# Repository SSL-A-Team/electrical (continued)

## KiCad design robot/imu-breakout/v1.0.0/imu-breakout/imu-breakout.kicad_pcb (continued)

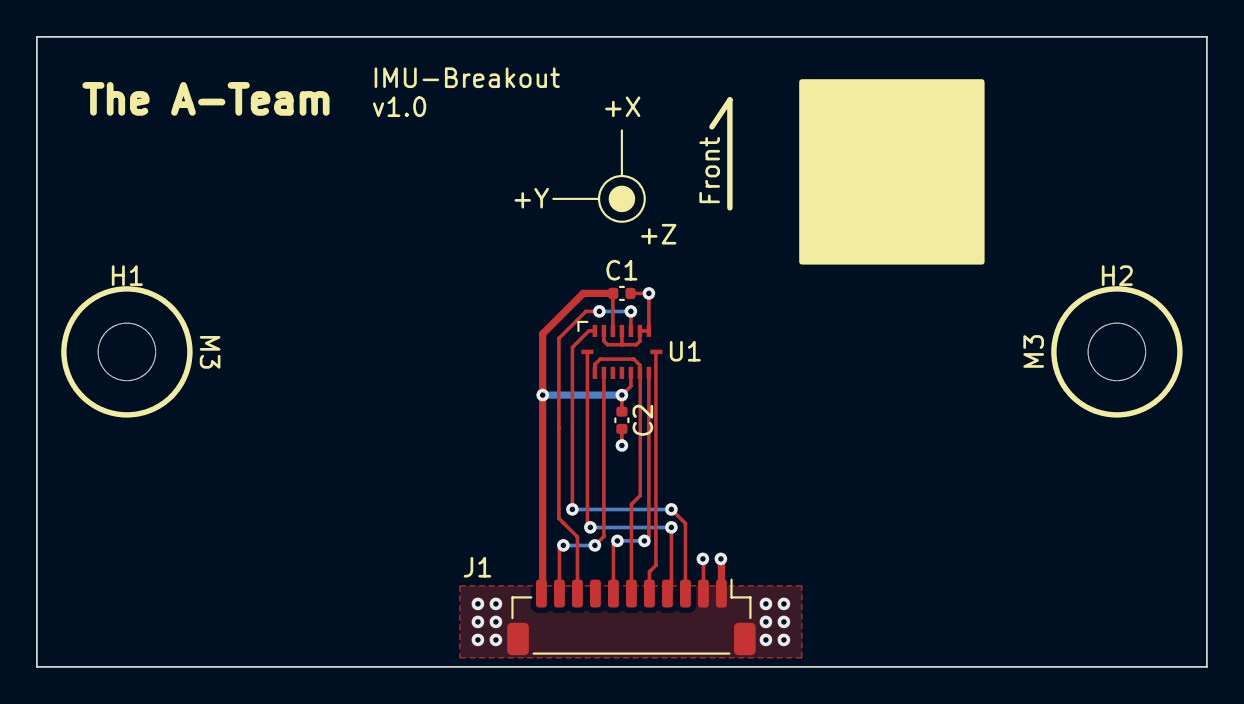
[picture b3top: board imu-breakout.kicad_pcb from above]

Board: 2 copper layers, 65.0 x 35.0 mm, 6 parts (0 on the bottom side), 9 nets.

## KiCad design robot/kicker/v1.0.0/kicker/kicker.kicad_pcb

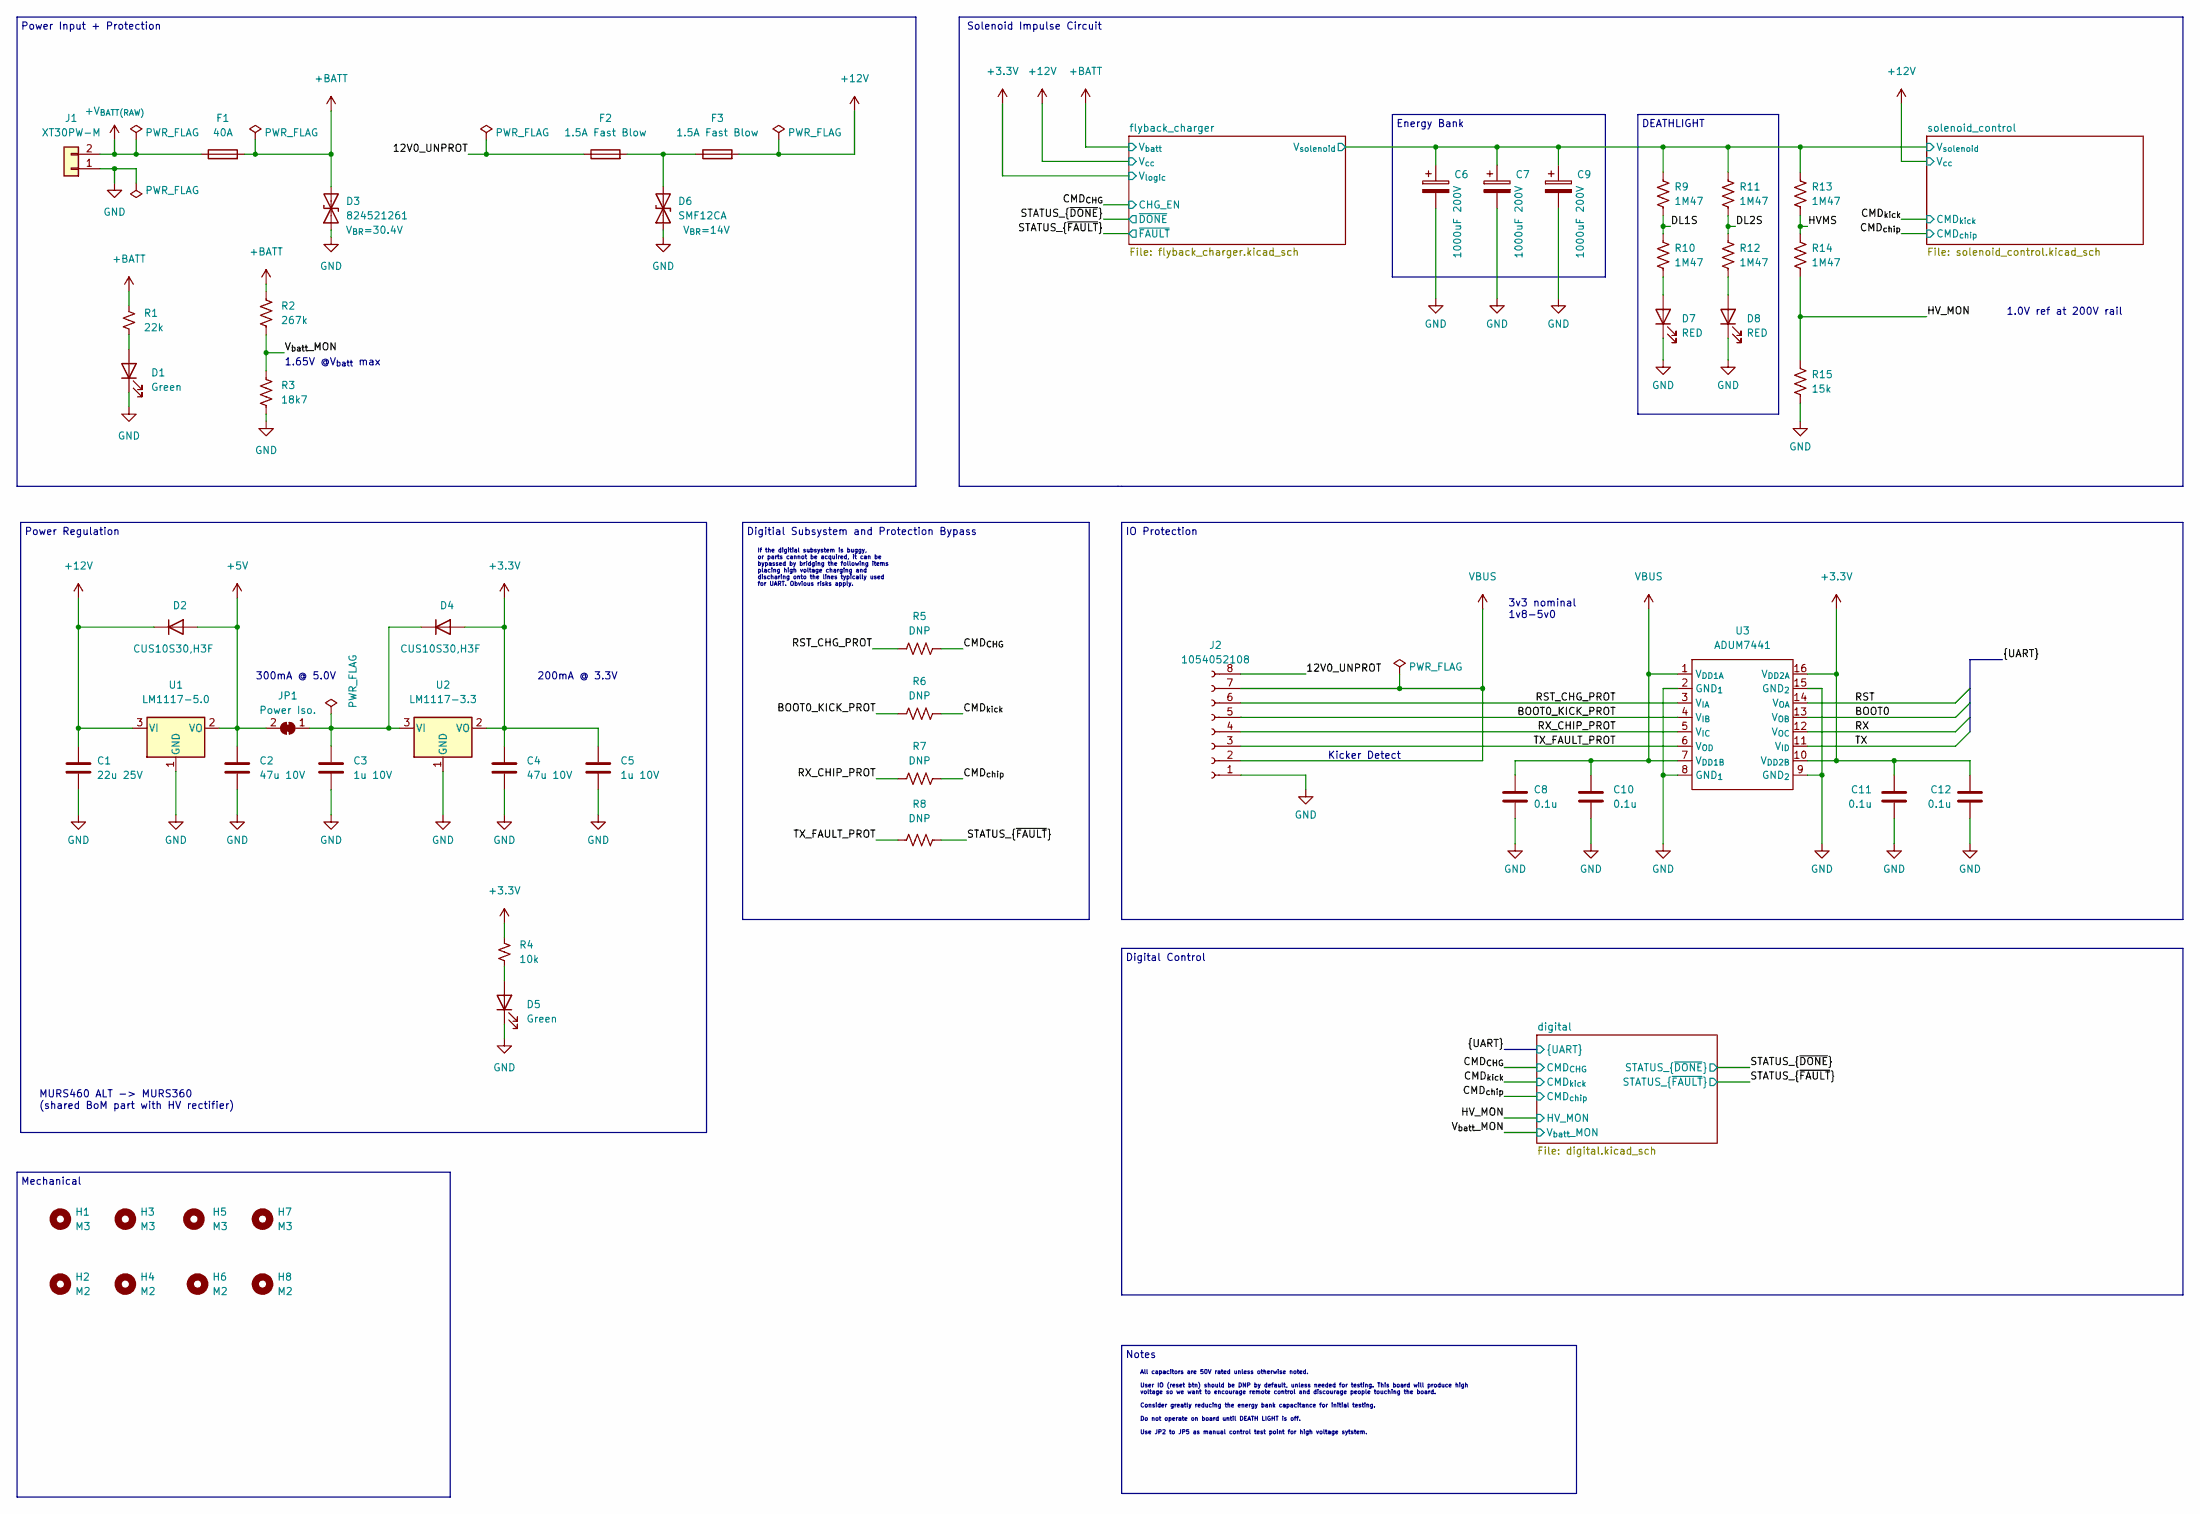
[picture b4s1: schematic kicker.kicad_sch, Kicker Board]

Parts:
C1: 22u 25V; C_1210_3225Metric
C2, C4: 47u 10V; C_1210_3225Metric
C3, C5: 1u 10V; C_0603_1608Metric
C6, C7, C9: 1000uF 200V; ESMQ201VSN102MQ35S
C8, C10, C11, C12: 0.1u; C_0603_1608Metric
D1, D5: Green; LED0603
D2, D4: CUS10S30,H3F; D_SOD-323
D3: 824521261; D_SMB_Non-Polar
D6: SMF12CA; D_SOD-123F
D7, D8: RED; LED0603
F1: 40A; 3557-2
F2, F3: 1.5A Fast Blow; Fuse_0603_1608Metric
H1, H3, H5, H7: M3; MountingHole_3.2mm_M3_ISO7380_Pad_TopBottom
H2, H4, H6, H8: M2; MountingHole_2.2mm_M2_ISO14580_Pad_TopBottom
J1: XT30PW-M; AMASS_XT30PW-M_1x02_P2.50mm_Horizontal
J2: 1054052108; JST_SH_BM08B-SRSS-TB_1x08-1MP_P1.00mm_Vertical
JP1: Power Iso.; SolderJumper-2_P1.3mm_Bridged_RoundedPad1.0x1.5mm
R1: 22k; R_0603_1608Metric
R2: 267k; R_0603_1608Metric
R3: 18k7; R_0603_1608Metric
R4: 10k; R_0603_1608Metric
R5, R6, R7, R8: DNP; R_0603_1608Metric
R9, R10, R11, R12, R13, R14: 1M47; R_0603_1608Metric
R15: 15k; R_0603_1608Metric
U1: LM1117-5.0; TO-252-2
U2: LM1117-3.3; SOT-223-3_TabPin2
U3: ADUM7441; QSOP-16_3.9x4.9mm_P0.635mm

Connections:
+3V3: C4.1, C5.1, C11.1, C12.1, D4.2 (A), R4.1, U2.2 (VO), U3.10 (V_{DD2B}), U3.16 (V_{DD2A}); also elsewhere on the board
+5V: C2.1, D2.2 (A), JP1.2 (B), U1.2 (VO); also elsewhere on the board
+12V: C1.1, D2.1 (K), F3.2, U1.3 (VI); also elsewhere on the board
+BATT: D3.2 (A2), F1.2, R1.1, R2.1; also elsewhere on the board
+V_{BATT(RAW)}: F1.1, J1.2
/12V0_UNPROT: F2.1, J2.8
/BOOT0: U3.13 (V_{OB}); also elsewhere on the board
/BOOT0_KICK_PROT: J2.5, R6.1, U3.4 (V_{IB})
/CMD_{CHG}: R5.2; also elsewhere on the board
/CMD_{chip}: R7.2; also elsewhere on the board
/CMD_{kick}: R6.2; also elsewhere on the board
/DL1S: R9.2, R10.1
/DL2S: R11.2, R12.1
/HVMS: R13.2, R14.1
/HV_MON: R14.2, R15.1; also elsewhere on the board
/RST: U3.14 (V_{OA}); also elsewhere on the board
/RST_CHG_PROT: J2.6, R5.1, U3.3 (V_{IA})
/RX: U3.12 (V_{OC}); also elsewhere on the board
/RX_CHIP_PROT: J2.4, R7.1, U3.5 (V_{IC})
/STATUS_{~FAULT}: R8.2; also elsewhere on the board
/TX: U3.11 (V_{ID}); also elsewhere on the board
/TX_FAULT_PROT: J2.3, R8.1, U3.6 (V_{OD})
/V_{batt}_MON: R2.2, R3.1; also elsewhere on the board
/flyback_charger/V_{solenoid}: C6.1, C7.1, C9.1, R9.1, R11.1, R13.1; also elsewhere on the board
GND: C1.2, C2.2, C3.2, C4.2, C5.2, C6.2, C7.2, C8.2, C9.2, C10.2, C11.2, C12.2, D1.1 (K), D3.1 (A1), D5.1 (K), D6.1 (A1), D7.1 (K), D8.1 (K), J1.1, J2.1, R3.2, R15.2, U1.1 (GND), U2.1 (GND), U3.2 (GND_{1}), U3.8 (GND_{1}), U3.9 (GND_{2}), U3.15 (GND_{2}); also elsewhere on the board
unnamed: C3.1, D4.1 (K), JP1.1 (A), U2.3 (VI)
unnamed: D1.2 (A), R1.2
unnamed: D5.2 (A), R4.2
unnamed: D6.2 (A2), F2.2, F3.1
unnamed: D7.2 (A), R10.2
unnamed: D8.2 (A), R12.2
VBUS: C8.1, C10.1, J2.2, J2.7, U3.1 (V_{DD1A}), U3.7 (V_{DD1B})

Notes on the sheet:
Solenoid Impulse Circuit
If the digitial subsystem is buggy, or parts cannot be acquired, it can be bypassed by bridging the following items placing high voltage charging and discharing onto the lines typically used for UART. Obvious risks apply.
All capacitors are 50V rated unless otherwise noted. User IO (reset btn) should be DNP by default, unless needed for testing. This board will produce high voltage so we want to encourage remote control and discourage people touching the board. Consider greatly reducing the energy bank capacitance f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
Notes
Energy Bank
Power Input + Protection
Power Regulation
MURS460 ALT -> MURS360 (shared BoM part with HV rectifier)
200mA @ 3.3V
DEATHLIGHT
Mechanical
Kicker Detect
1.65V @V_{batt} max
1.0V ref at 200V rail
300mA @ 5.0V
Digital Control
IO Protection
3v3 nominal 1v8-5v0
Digitial Subsystem and Protection Bypass

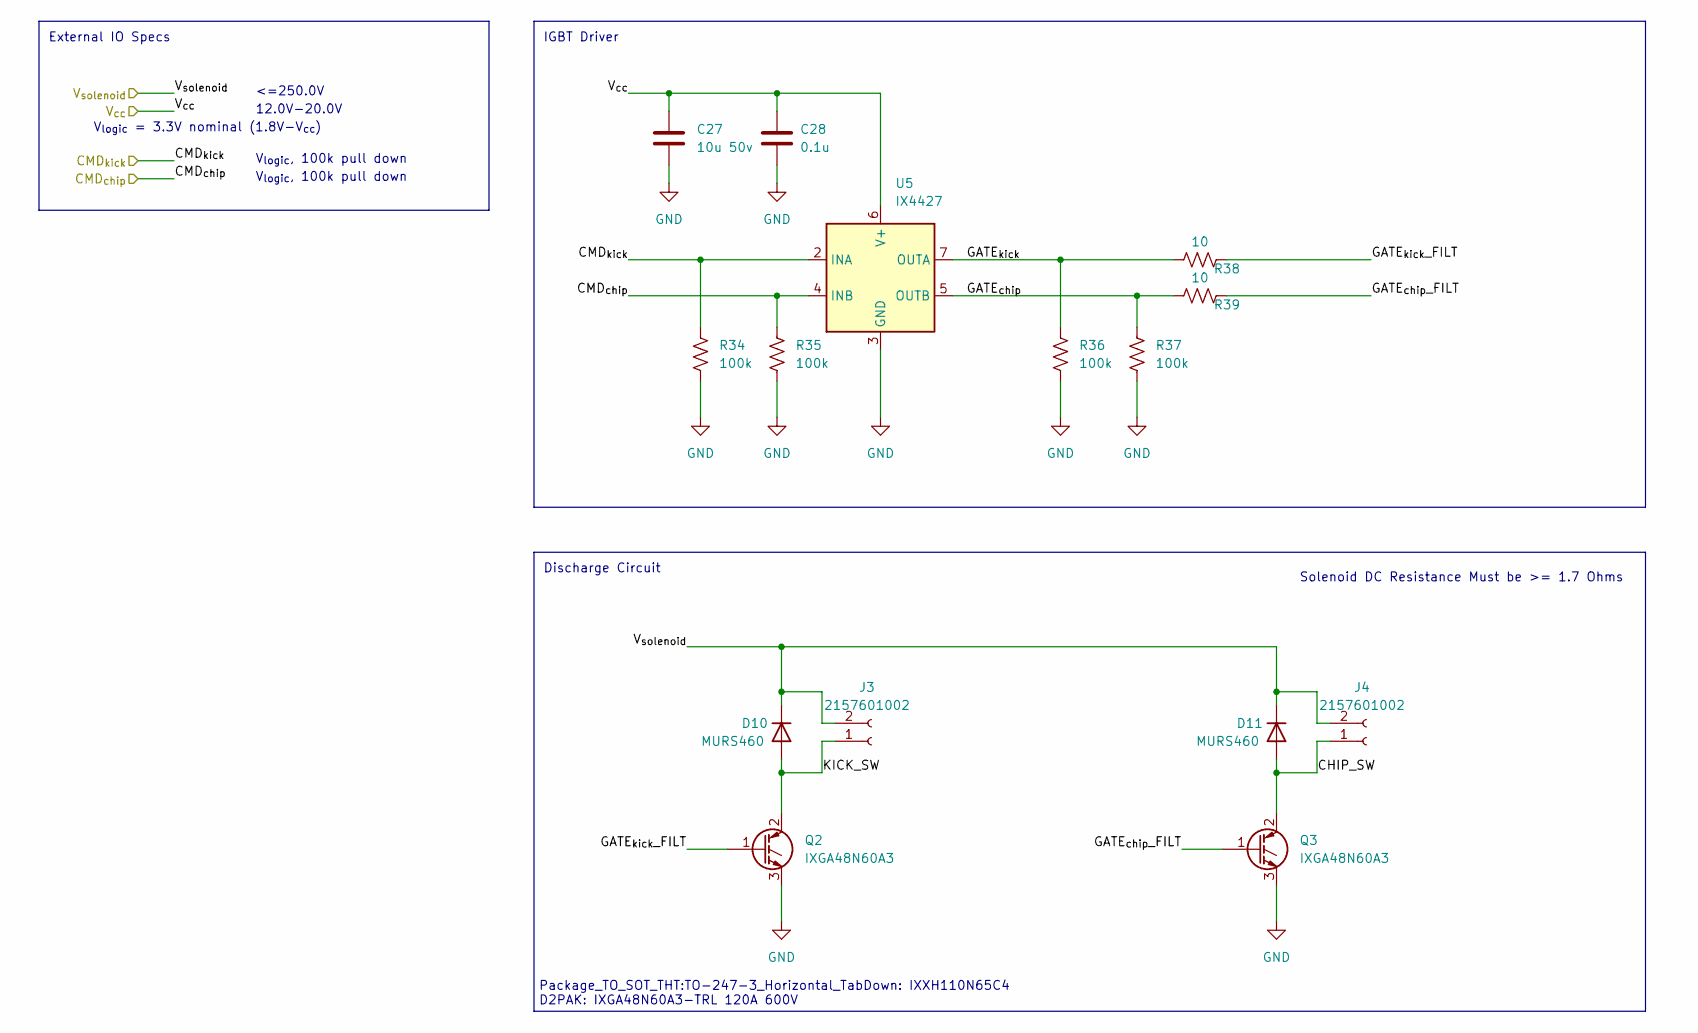
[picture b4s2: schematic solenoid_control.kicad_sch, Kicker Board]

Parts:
C27: 10u 50v; C_1210_3225Metric
C28: 0.1u; C_0603_1608Metric
D10, D11: MURS460; D_SMC
J3, J4: 2157601002
Q2, Q3: IXGA48N60A3; TO-263-2
R34, R35, R36, R37: 100k; R_0603_1608Metric
R38, R39: 10; R_0603_1608Metric
U5: IX4427; SOIC-8_3.9x4.9mm_P1.27mm

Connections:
+12V: C27.1, C28.1, U5.6 (V+); also elsewhere on the board
/CMD_{chip}: R35.1, U5.4 (INB); also elsewhere on the board
/CMD_{kick}: R34.1, U5.2 (INA); also elsewhere on the board
/flyback_charger/V_{solenoid}: D10.1 (K), D11.1 (K), J3.2, J4.2; also elsewhere on the board
/solenoid_control/CHIP_SW: D11.2 (A), J4.1, Q3.2 (C)
/solenoid_control/GATE_{chip}: R37.1, R39.1, U5.5 (OUTB)
/solenoid_control/GATE_{chip}_FILT: Q3.1 (G), R39.2
/solenoid_control/GATE_{kick}: R36.1, R38.1, U5.7 (OUTA)
/solenoid_control/GATE_{kick}_FILT: Q2.1 (G), R38.2
/solenoid_control/KICK_SW: D10.2 (A), J3.1, Q2.2 (C)
GND: C27.2, C28.2, Q2.3 (E), Q3.3 (E), R34.2, R35.2, R36.2, R37.2, U5.3 (GND); also elsewhere on the board

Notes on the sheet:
Solenoid DC Resistance Must be >= 1.7 Ohms
IGBT Driver
12.0V-20.0V
V_{logic}, 100k pull down
External IO Specs
Discharge Circuit
Package_TO_SOT_THT:TO-247-3_Horizontal_TabDown: IXXH110N65C4 D2PAK: IXGA48N60A3-TRL 120A 600V
<=250.0V
V_{logic} = 3.3V nominal (1.8V-V_{cc})

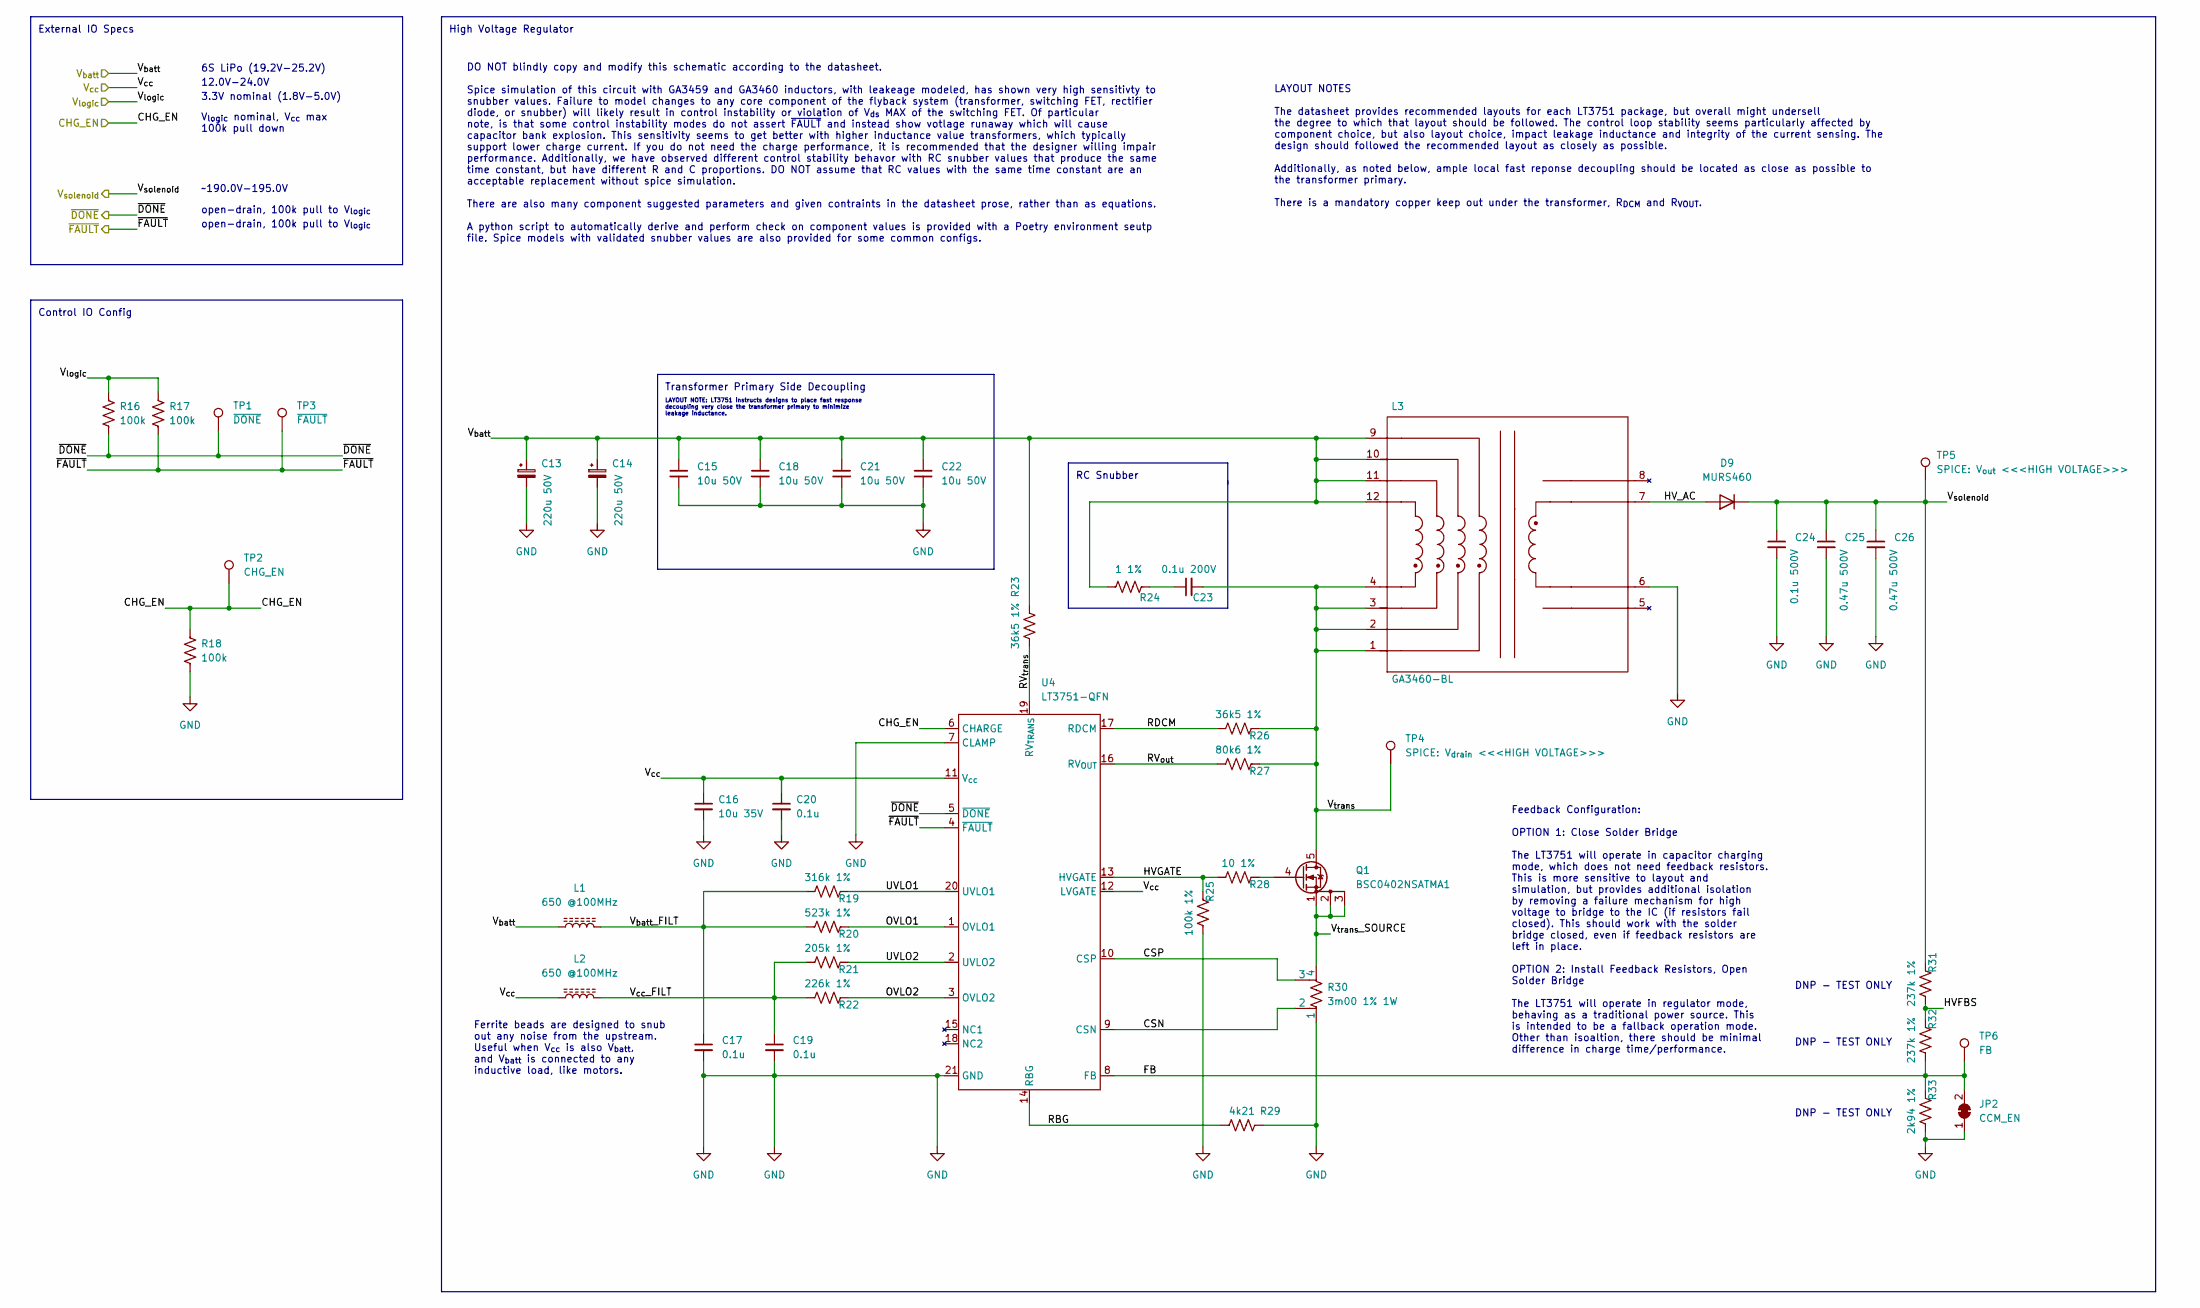
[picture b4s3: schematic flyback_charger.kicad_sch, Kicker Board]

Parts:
C13, C14: 220u 50V; CP_Radial_D10.0mm_P5.00mm
C15, C18, C21, C22: 10u 50V; C_1210_3225Metric
C16: 10u 35V; C_1206_3216Metric
C17, C19, C20: 0.1u; C_0603_1608Metric
C23: 0.1u 200V; C_1206_3216Metric
C24: 0.1u 500V; C_1210_3225Metric
C25, C26: 0.47u 500V; C_2225_5664Metric
D9: MURS460; D_SMC
JP2: CCM_EN; SolderJumper-2_P1.3mm_Bridged_RoundedPad1.0x1.5mm
L1, L2: 650 @100MHz; R_0603_1608Metric
L3: GA3460-BL; GA34XX-BL
Q1: BSC0402NSATMA1; TDSON-8-1
R16, R17, R18: 100k; R_0603_1608Metric
R19: 316k 1%; R_0603_1608Metric
R20: 523k 1%; R_0603_1608Metric
R21: 205k 1%; R_0603_1608Metric
R22: 226k 1%; R_0603_1608Metric
R23, R26: 36k5 1%; R_0603_1608Metric
R24: 1 1%; R_0805_2012Metric
R25: 100k 1%; R_0603_1608Metric
R27: 80k6 1%; R_0603_1608Metric
R28: 10 1%; R_0603_1608Metric
R29: 4k21; R_0603_1608Metric
R30: 3m00 1% 1W; 1206-CS
R31, R32: 237k 1%; R_0603_1608Metric
R33: 2k94 1%; R_0603_1608Metric
TP1: ~{DONE}; TestPoint_Pad_D1.5mm
TP2: CHG_EN; TestPoint_Pad_D1.5mm
TP3: ~{FAULT}; TestPoint_Pad_D1.5mm
TP4: SPICE: V_{drain} <<<HIGH VOLTAGE>>>; TestPoint_Pad_D1.0mm
TP5: SPICE: V_{out} <<<HIGH VOLTAGE>>>; TestPoint_Pad_D1.5mm
TP6: FB; TestPoint_Pad_D1.5mm
U4: LT3751-QFN; LT3751-QFN20_EP_4x5mm_P0.5mm

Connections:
+3V3: R16.1, R17.1; also elsewhere on the board
+12V: C16.1, C20.1, L2.1, U4.11 (V_{cc}), U4.12 (LVGATE); also elsewhere on the board
+BATT: C13.1, C14.1, C15.1, C18.1, C21.1, C22.1, L1.1, L3.9, L3.10, L3.11, L3.12, R23.2, R24.1; also elsewhere on the board
/CMD_{CHG}: R18.1, TP2.1, U4.6 (CHARGE); also elsewhere on the board
/STATUS_{~DONE}: R16.2, TP1.1, U4.5 (~DONE); also elsewhere on the board
/STATUS_{~FAULT}: R17.2, TP3.1, U4.4 (~FAULT); also elsewhere on the board
/flyback_charger/CSN: R30.2, U4.9 (CSN)
/flyback_charger/CSP: R30.3, U4.10 (CSP)
/flyback_charger/FB: JP2.2 (B), R32.1, R33.2, TP6.1, U4.8 (FB)
/flyback_charger/HVFBS: R31.1, R32.2
/flyback_charger/HVGATE: R25.2, R28.1, U4.13 (HVGATE)
/flyback_charger/HV_AC: D9.2 (A), L3.7
/flyback_charger/OVLO1: R20.2, U4.1 (OVLO1)
/flyback_charger/OVLO2: R22.2, U4.3 (OVLO2)
/flyback_charger/RBG: R29.1, U4.14 (RBG)
/flyback_charger/RDCM: R26.1, U4.17 (RDCM)
/flyback_charger/RV_{out}: R27.1, U4.16 (RV_{OUT})
/flyback_charger/RV_{trans}: R23.1, U4.19 (RV_{TRANS})
/flyback_charger/UVLO1: R19.2, U4.20 (UVLO1)
/flyback_charger/UVLO2: R21.2, U4.2 (UVLO2)
/flyback_charger/V_{batt}_FILT: C17.1, L1.2, R19.1, R20.1
/flyback_charger/V_{cc}_FILT: C19.1, L2.2, R21.1, R22.1
/flyback_charger/V_{solenoid}: C24.1, C25.1, C26.1, D9.1 (K), R31.2, TP5.1; also elsewhere on the board
/flyback_charger/V_{trans}: C23.2, L3.1, L3.2, L3.3, L3.4, Q1.5 (D), R26.2, R27.2, TP4.1
/flyback_charger/V_{trans}_SOURCE: Q1.1 (S), Q1.2 (S), Q1.3 (S), R30.4
GND: C13.2, C14.2, C15.2, C16.2, C17.2, C18.2, C19.2, C20.2, C21.2, C22.2, C24.2, C25.2, C26.2, JP2.1 (A), L3.6, R18.2, R25.1, R29.2, R30.1, R33.1, U4.7 (CLAMP), U4.21 (GND); also elsewhere on the board
unnamed: C23.1, R24.2
unnamed: Q1.4 (G), R28.2

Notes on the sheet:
Ferrite beads are designed to snub out any noise from the upstream. Useful when V_{cc} is also V_{batt}, and V_{batt} is connected to any inductive load, like motors.
DO NOT blindly copy and modify this schematic according to the datasheet. Spice simulation of this circuit with GA3459 and GA3460 inductors, with leakeage modeled, has shown very high sensitivty to snubber values. Failure to model changes to any core component of the flyback system (transformer, sw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
DNP - TEST ONLY
High Voltage Regulator
LAYOUT NOTE: LT3751 instructs designs to place fast response decoupling very close the transformer primary to minimize leakage inductance.
Control IO Config
6S LiPo (19.2V-25.2V)
~190.0V-195.0V
12.0V-24.0V
open-drain, 100k pull to V_{logic}
External IO Specs
LAYOUT NOTES The datasheet provides recommended layouts for each LT3751 package, but overall might undersell the degree to which that layout should be followed. The control loop stability seems particularly affected by component choice, but also layout choice, impact leakage inductance and integrit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
V_{logic} nominal, V_{cc} max 100k pull down
Transformer Primary Side Decoupling
3.3V nominal (1.8V-5.0V)
Feedback Configuration: OPTION 1: Close Solder Bridge The LT3751 will operate in capacitor charging mode, which does not need feedback resistors. This is more sensitive to layout and simulation, but provides additional isolation by removing a failure mechanism for high voltage to bridge to the IC (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
RC Snubber

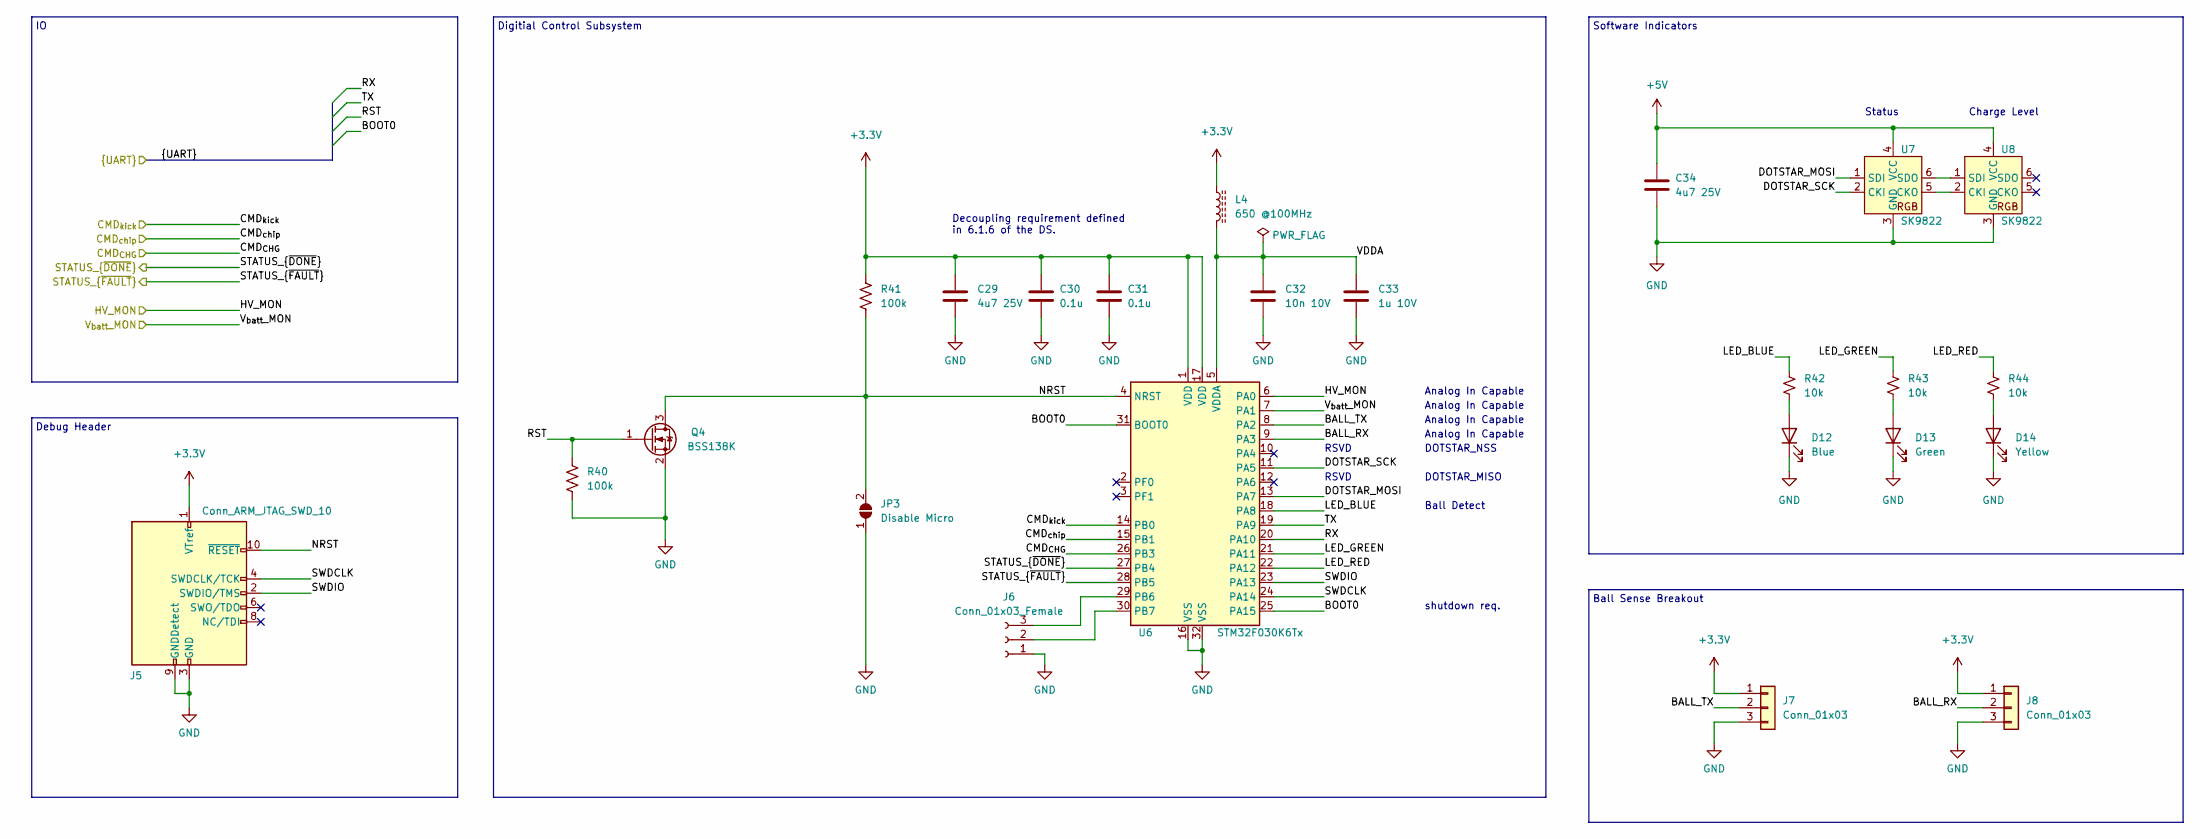
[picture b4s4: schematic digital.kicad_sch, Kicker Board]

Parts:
C29, C34: 4u7 25V; C_0805_2012Metric
C30, C31: 0.1u; C_0603_1608Metric
C32: 10n 10V; C_0603_1608Metric
C33: 1u 10V; C_0603_1608Metric
D12: Blue; LED0603
D13: Green; LED0603
D14: Yellow; LED0603
J5: Conn_ARM_JTAG_SWD_10; Samtec-2x5pin-0.5mm
J6: Conn_01x03_Female; PinHeader_1x03_P1.27mm_Vertical
J7, J8: Conn_01x03; JST_SH_SM03B-SRSS-TB_1x03-1MP_P1.00mm_Horizontal
JP3: Disable Micro; SolderJumper-2_P1.3mm_Open_RoundedPad1.0x1.5mm
L4: 650 @100MHz; R_0603_1608Metric
Q4: BSS138K; SOT-23
R40, R41: 100k; R_0603_1608Metric
R42, R43, R44: 10k; R_0603_1608Metric
U6: STM32F030K6Tx; LQFP-32_7x7mm_P0.8mm
U7, U8: SK9822

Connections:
+3V3: C29.1, C30.1, C31.1, J5.1 (VTref), J7.1, J8.1, L4.1, R41.1, U6.1 (VDD), U6.17 (VDD); also elsewhere on the board
+5V: C34.2, U7.4 (VCC), U8.4 (VCC); also elsewhere on the board
/BOOT0: U6.25 (PA15), U6.31 (BOOT0); also elsewhere on the board
/CMD_{CHG}: U6.26 (PB3); also elsewhere on the board
/CMD_{chip}: U6.15 (PB1); also elsewhere on the board
/CMD_{kick}: U6.14 (PB0); also elsewhere on the board
/HV_MON: U6.6 (PA0); also elsewhere on the board
/RST: Q4.1 (G), R40.1; also elsewhere on the board
/RX: U6.20 (PA10); also elsewhere on the board
/STATUS_{~DONE}: U6.27 (PB4); also elsewhere on the board
/STATUS_{~FAULT}: U6.28 (PB5); also elsewhere on the board
/TX: U6.19 (PA9); also elsewhere on the board
/V_{batt}_MON: U6.7 (PA1); also elsewhere on the board
/digital/BALL_RX: J8.2, U6.9 (PA3)
/digital/BALL_TX: J7.2, U6.8 (PA2)
/digital/DOTSTAR_MOSI: U6.13 (PA7), U7.1 (SDI)
/digital/DOTSTAR_SCK: U6.11 (PA5), U7.2 (CKI)
/digital/LED_BLUE: R42.1, U6.18 (PA8)
/digital/LED_GREEN: R43.1, U6.21 (PA11)
/digital/LED_RED: R44.1, U6.22 (PA12)
/digital/NRST: J5.10 (~RESET), JP3.2 (B), Q4.3 (D), R41.2, U6.4 (NRST)
/digital/SWDCLK: J5.4 (SWDCLK/TCK), U6.24 (PA14)
/digital/SWDIO: J5.2 (SWDIO/TMS), U6.23 (PA13)
/digital/VDDA: C32.1, C33.1, L4.2, U6.5 (VDDA)
GND: C29.2, C30.2, C31.2, C32.2, C33.2, C34.1, D12.1 (K), D13.1 (K), D14.1 (K), J5.3 (GND), J5.5 (GND), J5.9 (GNDDetect), J6.1, J7.3, J8.3, JP3.1 (A), Q4.2 (S), R40.2, U6.16 (VSS), U6.32 (VSS), U7.3 (GND), U8.3 (GND); also elsewhere on the board
unnamed: D12.2 (A), R42.2
unnamed: D13.2 (A), R43.2
unnamed: D14.2 (A), R44.2
unnamed: J6.3, U6.29 (PB6)
unnamed: J6.2, U6.30 (PB7)
unnamed: U7.5 (CKO), U8.2 (CKI)
unnamed: U7.6 (SDO), U8.1 (SDI)

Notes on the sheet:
shutdown req.
Analog In Capable
Ball Sense Breakout
Debug Header
DOTSTAR_NSS
Charge Level
Decoupling requirement defined in 6.1.6 of the DS.
RSVD
Status
Digitial Control Subsystem
Ball Detect
DOTSTAR_MISO
Software Indicators

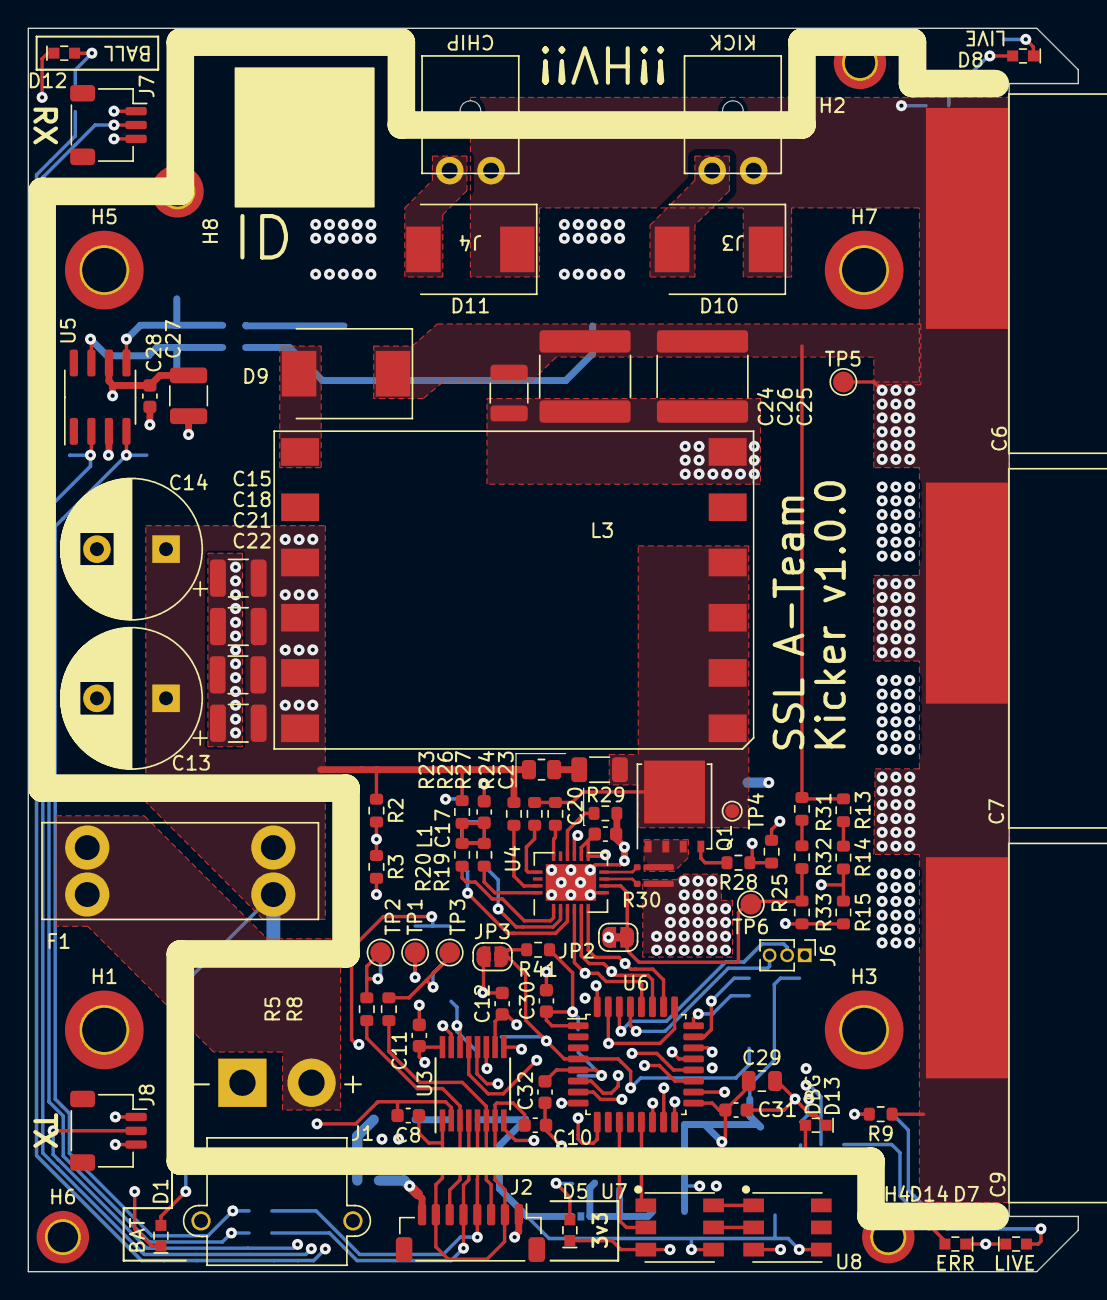
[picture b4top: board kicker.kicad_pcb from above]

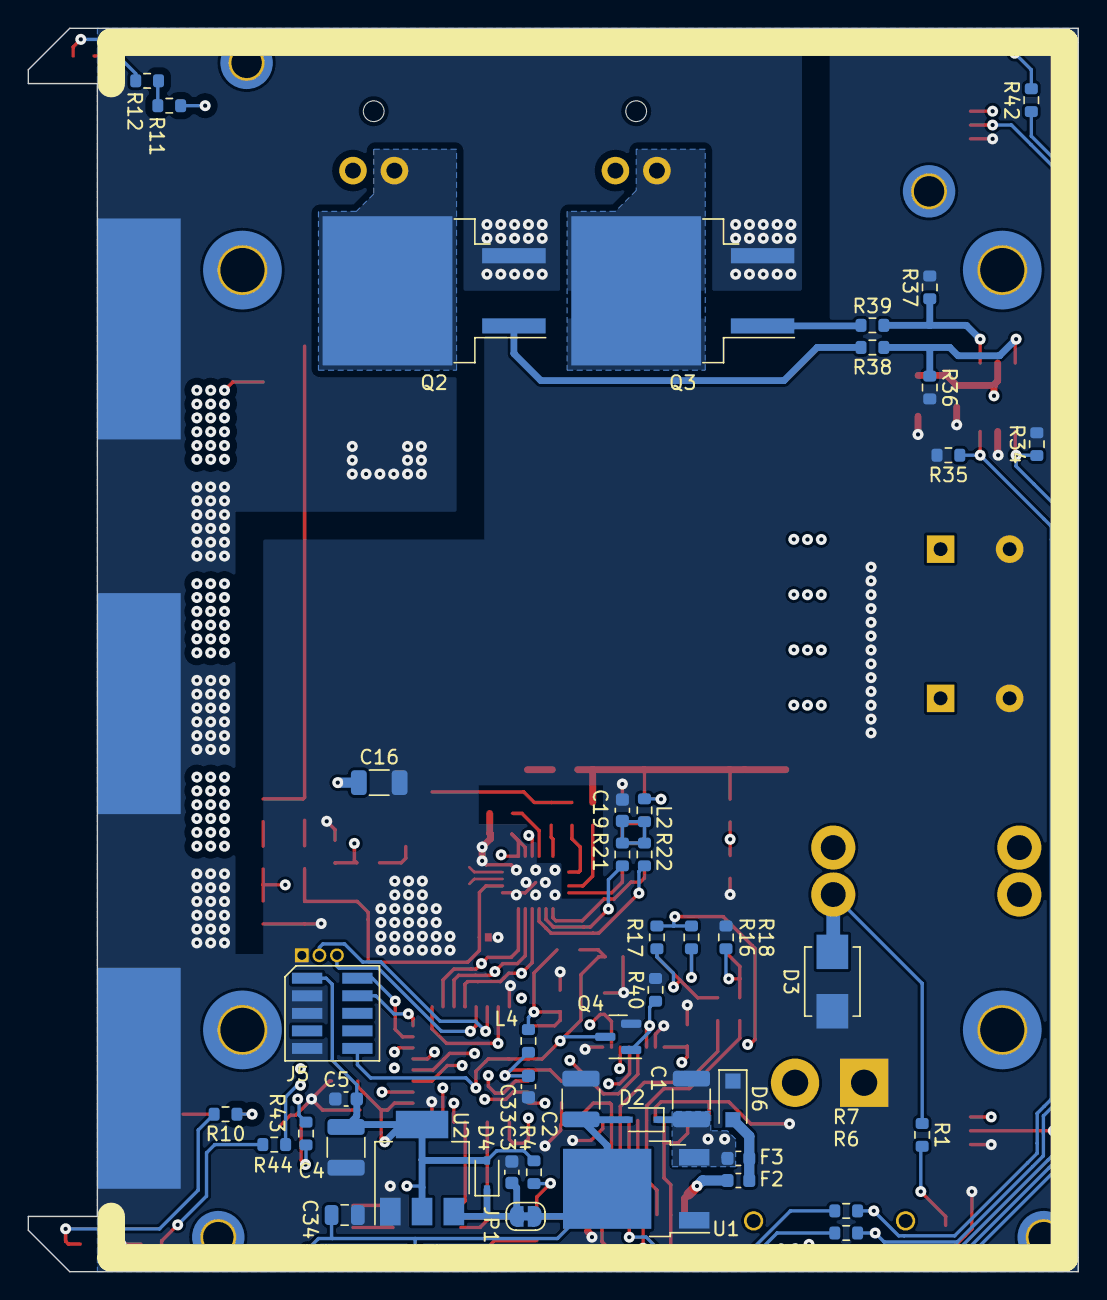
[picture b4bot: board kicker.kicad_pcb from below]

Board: 4 copper layers, 76.0 x 90.0 mm, 136 parts (46 on the bottom side), 77 nets.

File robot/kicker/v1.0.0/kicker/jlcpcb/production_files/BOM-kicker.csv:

Comment,Designator,Footprint,LCSC
10 1%,"R28,R38,R39",R_0603_1608Metric,C109318
0.1u 200V,C23,C_1206_3216Metric,C113894
15k,R15,R_0603_1608Metric,C114661
Blue,D12,LED0603,C131231
10u 35V,C16,C_1206_3216Metric,C13585
4k21,R29,R_0603_1608Metric,C137713
36k5 1%,"R23,R26",R_0603_1608Metric,C137738
2k94 1%,R33,R_0603_1608Metric,C137748
0.1u 500V,C24,C_1210_3225Metric,C141218
1 1%,R24,R_0805_2012Metric,C144579
0.47u 500V,"C25,C26",C_2225_5664Metric,C146186
"CUS10S30,H3F","D2,D4",D_SOD-323,C146335
0.1u,"C10,C11,C12,C17,C19,C20,C28,C30,C31,C8",C_0603_1608Metric,C14663
100k,"R16,R17,R18,R25,R34,R35,R36,R37,R40,R41",R_0603_1608Metric,C14675
226k 1%,R22,R_0603_1608Metric,C165744
IX4427,U5,SOIC-8_3.9x4.9mm_P1.27mm,C171845
4u7 25V,"C29,C34",C_0805_2012Metric,C1779
523k 1%,R20,R_0603_1608Metric,C185324
316k 1%,R19,R_0603_1608Metric,C185340
205k 1%,R21,R_0603_1608Metric,C185351
10u 50V,"C15,C18,C21,C22,C27",C_1210_3225Metric,C18739
237k 1%,"R31,R32",R_0603_1608Metric,C188262
18k7,R3,R_0603_1608Metric,C227631
267k,R2,R_0603_1608Metric,C227741
80k6 1%,R27,R_0603_1608Metric,C228066
LM1117-3.3,U2,SOT-223-3_TabPin2,C23984
BSS138K,Q4,SOT-23,C255592
10k,"R4,R42,R43,R44",R_0603_1608Metric,C25804
1u 10V,"C3,C33,C5",C_0603_1608Metric,C26413
RED,"D7,D8",LED0603,C264440
SK9822,"U7,U8",SK9822,C2909059
22u 25V,C1,C_1210_3225Metric,C309062
22k,R1,R_0603_1608Metric,C31850
1M47,"R10,R11,R12,R13,R14,R9",R_0603_1608Metric,C482635
10n 10V,C32,C_0603_1608Metric,C519405
ADUM7441,U3,QSOP-16_3.9x4.9mm_P0.635mm,C661776
Yellow,D14,LED0603,C72038
Green,"D1,D13,D5",LED0603,C72043
STM32F030K6Tx,U6,LQFP-32_7x7mm_P0.8mm,C88446
650 @100MHz,"L1,L2,L4",R_0603_1608Metric,C88976
SMF12CA,D6,D_SOD-123F,C920181
47u 10V,"C2,C4",C_1210_3225Metric,C96123
MURS460,"D10,D11,D9",D_SMC,C961891
